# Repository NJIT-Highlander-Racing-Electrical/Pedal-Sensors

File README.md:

# Pedal-Sensors

A subsystem that measures the angle of the accelerator and brake pedal. These values are sent via the CAN-Bus to other subsystems on the vehicle and the DAS. 
 
## 2024-2025 Design Goals

* Use [PSC360G2-F2AA-C0002-ERA360-05K](https://www.newark.com/amphenol-piher-sensorscontrols/psc360g2-f2aa-c0002-era360-05k/mag-rotary-angle-position-sensor/dp/71AC5626) from Newark Electronics (roughly $15)
   * This specific model has the following parameters:
      * Redundant Output
          * Analogic Output
          * One goes 90% to 10% voltage output from 0 degrees to 360 degrees
          * Other output goes 10% to 90% voltage output from 0 degrees to 360 degrees
      * 360 Degrees sensing range
      * 5V Opearting Voltage

## 2025-2026

Perhaps it would be worth looking into using [these linear hall sensors](https://www.mouser.com/ProductDetail/Amphenol-Piher/PS2P-LIN-CE-M002-1A0-L0000-ELS120-05?qs=vLWxofP3U2wU68Sblifdzw%3D%3D&srsltid=AfmBOoohN6dBwwOQZAoPYRWV-dxtn3KejJmPO92qOBfPrXmIcMOC2kIM). Since there is no contact, and we are free to position the magnetic piece wherever, we could eliminate the need for complex mechanisms to convert linear motion to angular. Originally, we used that setup because there was a rotating bolt at the axis of rotation so there was no linear travel. However, now that the bolt is fixed, we cannot get an angular reading at the axis of rotation

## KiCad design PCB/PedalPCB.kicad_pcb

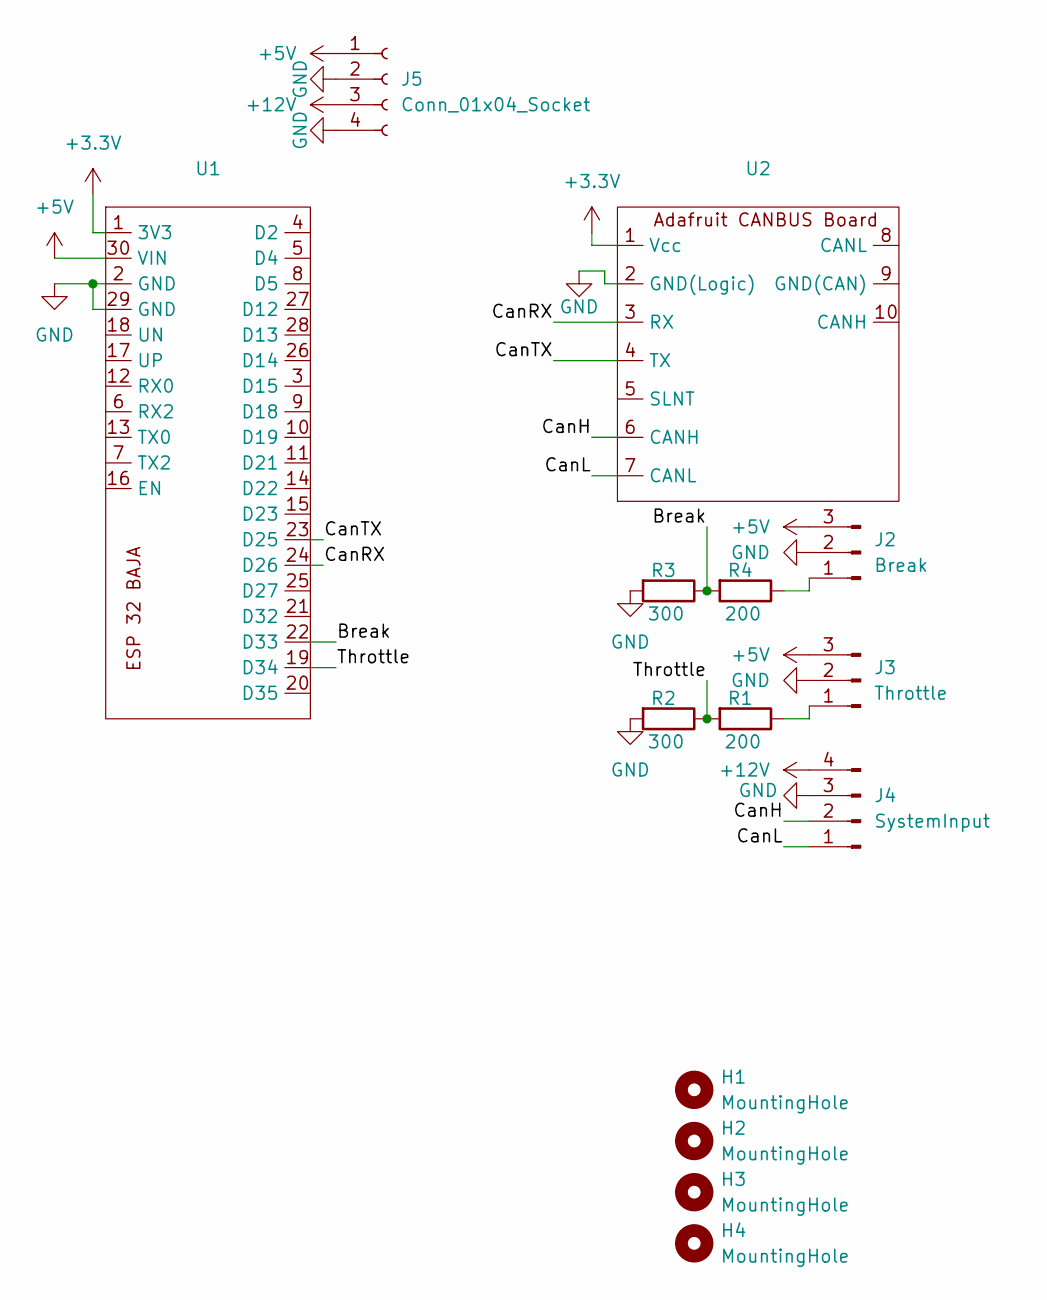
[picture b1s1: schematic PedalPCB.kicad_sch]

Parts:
H1, H2, H3, H4: MountingHole; MountingHole_4.3mm_M4
J2: Break; 3pin
J3: Throttle; 3pin
J4: SystemInput; JST4Pin
J5: Conn_01x04_Socket; PowerBoard
R1, R4: 200; R_Axial_DIN0204_L3.6mm_D1.6mm_P5.08mm_Horizontal
R2, R3: 300; R_Axial_DIN0204_L3.6mm_D1.6mm_P5.08mm_Horizontal
U1: ESP 32 BAJA
U2: 1x7 Connectors

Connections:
+3.3V: U1.1 (3V3), U2.1 (Vcc)
+5V: J2.3, J3.3, J5.1 (+5v), U1.30 (VIN)
+12V: J4.4, J5.3 (12+)
/Break: R3.1, R4.2, U1.22 (D33)
/CanH: J4.2, U2.6 (CANH)
/CanL: J4.1, U2.7 (CANL)
/CanRX: U1.24 (D26), U2.3 (RX)
/CanTX: U1.23 (D25), U2.4 (TX)
/Throttle: R1.2, R2.1, U1.19 (D34)
GND: J2.2, J3.2, J4.3, J5.2 (GND), J5.4 (GND), R2.2, R3.2, U1.2 (GND), U1.29 (GND), U2.2 (GND(Logic))
unnamed: J2.1, R4.1
unnamed: J3.1, R1.1

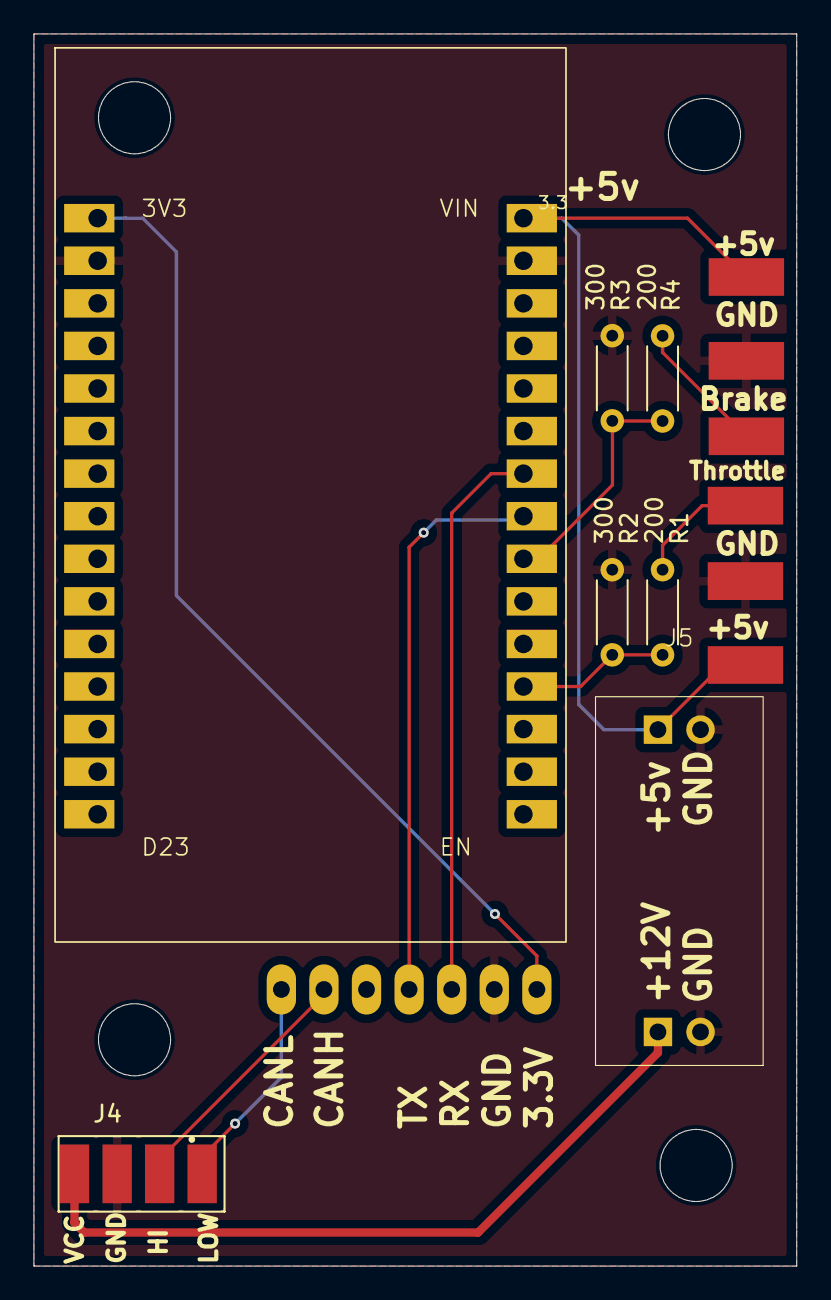
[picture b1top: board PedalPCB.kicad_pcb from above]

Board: 2 copper layers, 45.5 x 73.5 mm, 14 parts (1 on the bottom side), 12 nets.

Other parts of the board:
H1#2: MountingHole; MountingHole_4.3mm_M4

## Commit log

2024-10-20 Update Software Folder Layout
2024-11-17 Add first iteration of uniform enclosure design
2024-12-06 Add first version of pedal sensors code
2024-12-06 Update PCB to purchased version
2024-12-29 Update 3D Models
2025-01-07 Update to latest CAN driver
2025-01-08 Update to latest BajaCAN.h file
2025-03-29 Update to latest BajaCAN.h driver
2025-04-02 Update to latest CAN
2025-04-12 Update code to check brake pressure sensors
2025-04-12 Increase Serial Print rate to 460800
    So that way we spend less time printing and more time collecting data
2025-04-12 Add offset transformation for pressure sensors (see desc)
    Not sure why, but the analog reading value is consistently slightly less than it should be. Originally I though something was wrong with the voltage divider or software, but it appears to be an issue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
2025-04-19 Add 3d models
2025-05-04 Remove status bits
2025-05-10 Make pedal sensor reading only an int not a float
2025-05-11 revert to 500kpbs
2025-09-06 Uploaded latest CAN program (40Hz)
2025-09-06 Add DEBUG_SERIAL for disabling Serial in regular operation
2025-09-07 Remove useless link
2025-11-05 Replace old files with platformio project files
2025-11-05 add can library
